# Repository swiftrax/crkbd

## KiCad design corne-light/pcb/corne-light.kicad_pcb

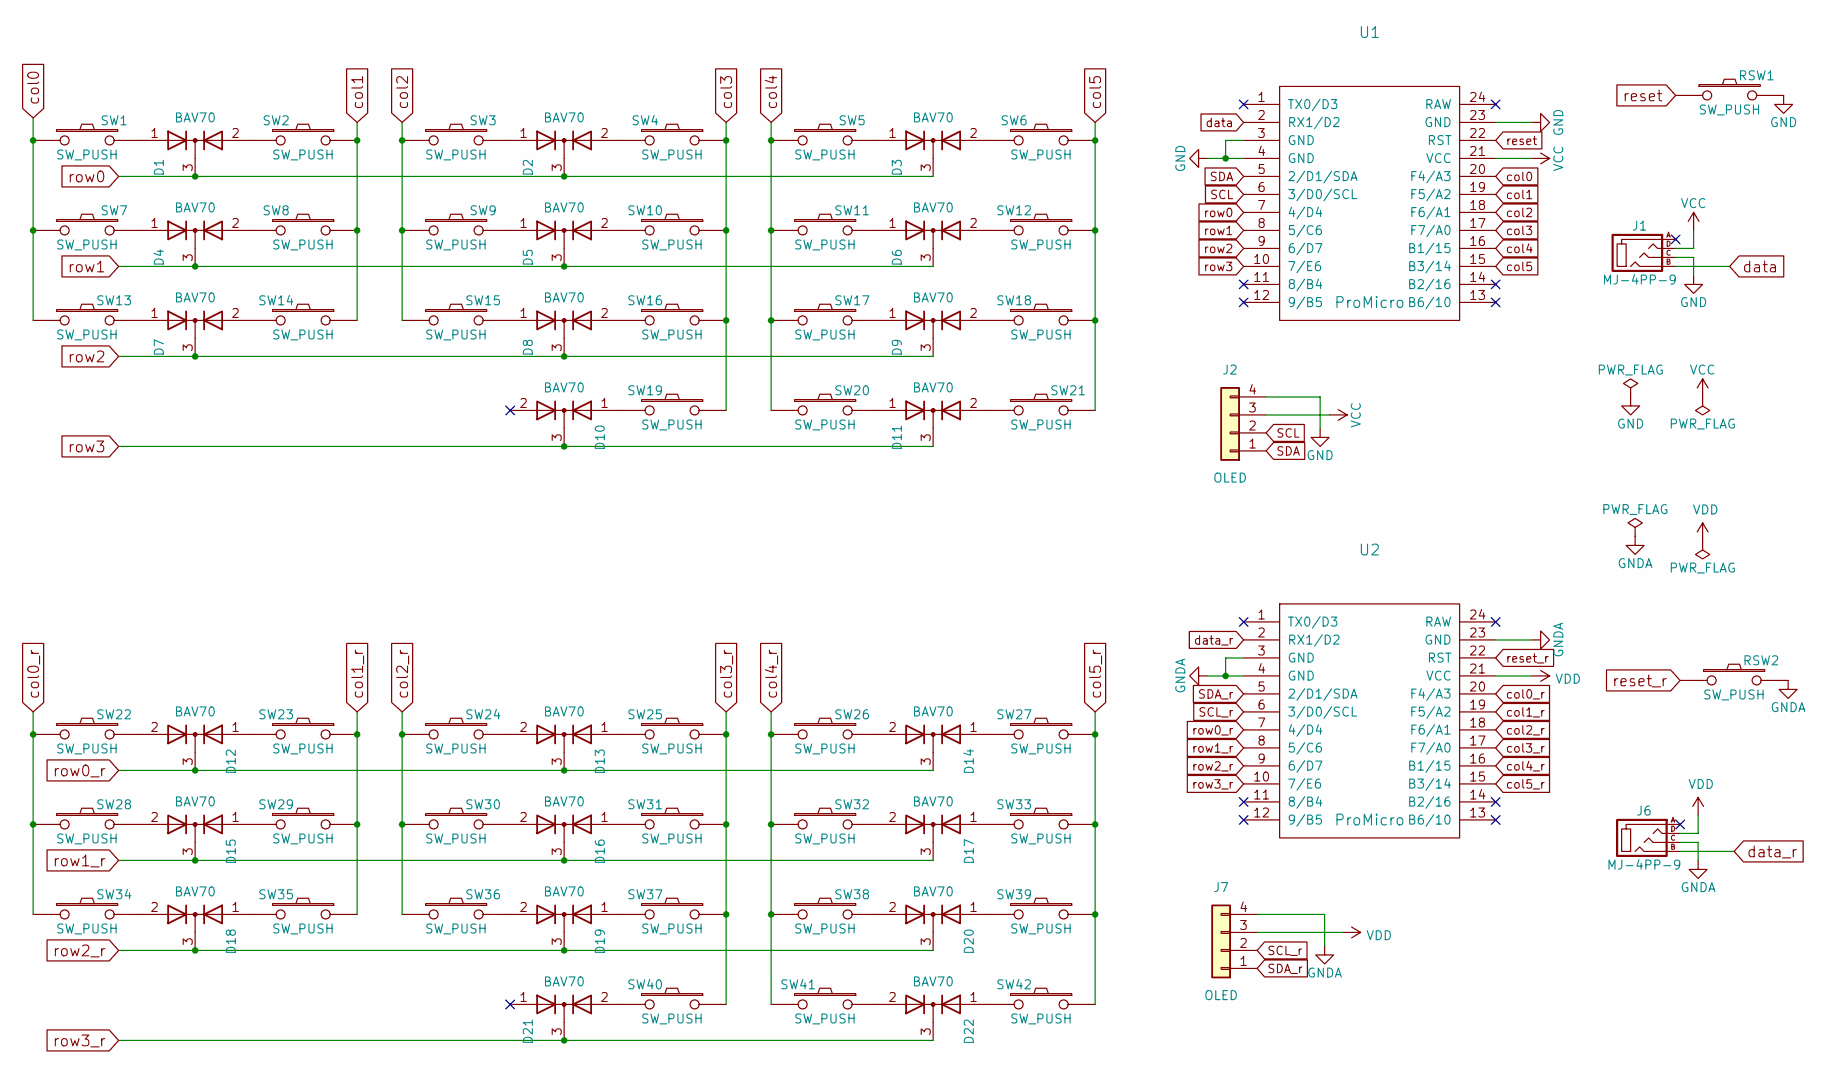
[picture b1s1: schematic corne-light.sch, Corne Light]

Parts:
D1, D2, D3, D4, D5, D6, D7, D8, D9, D10, D11, D12, D13, D14, D15, D16, D17, D18, D19, D20, D21, D22: BAV70; SOT-23_Annotated
J1, J6: MJ-4PP-9; MJ-4PP-9_1side
J2, J7: OLED; OLED_1side
RSW1, RSW2: SW_PUSH; ResetSW_1side
SW1, SW2, SW3, SW4, SW5, SW6, SW7, SW8, SW9, SW10, SW11, SW12, SW13, SW14, SW15, SW16, SW17, SW18, SW19, SW20, SW22, SW23, SW24, SW25, SW26, SW27, SW28, SW29, SW30, SW31, SW32, SW33, SW34, SW35, SW36, SW37, SW38, SW39, SW40, SW41: SW_PUSH; MXOnly-1U-NoLED
SW21, SW42: SW_PUSH; MXOnly-1.5U-NoLED
U1, U2: ProMicro; ProMicro_v3

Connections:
GND: J1.C, J2.4, RSW1.2, U1.3 (GND), U1.4 (GND), U1.23 (GND)
GNDA: J6.C, J7.4, RSW2.2, U2.3 (GND), U2.4 (GND), U2.23 (GND)
unnamed: D1.1 (A), SW1.2
unnamed: D1.2 (A), SW2.2
unnamed: D2.1 (A), SW3.2
unnamed: D2.2 (A), SW4.2
unnamed: D3.1 (A), SW5.2
unnamed: D3.2 (A), SW6.2
unnamed: D4.1 (A), SW7.2
unnamed: D4.2 (A), SW8.2
unnamed: D5.1 (A), SW9.2
unnamed: D5.2 (A), SW10.2
unnamed: D6.1 (A), SW11.2
unnamed: D6.2 (A), SW12.2
unnamed: D7.1 (A), SW13.2
unnamed: D7.2 (A), SW14.2
unnamed: D8.1 (A), SW15.2
unnamed: D8.2 (A), SW16.2
unnamed: D9.1 (A), SW17.2
unnamed: D9.2 (A), SW18.2
unnamed: D10.1 (A), SW19.2
unnamed: D11.1 (A), SW20.2
unnamed: D11.2 (A), SW21.1
unnamed: D12.1 (A), SW23.2
unnamed: D12.2 (A), SW22.2
unnamed: D13.1 (A), SW25.2
unnamed: D13.2 (A), SW24.2
unnamed: D14.1 (A), SW27.2
unnamed: D14.2 (A), SW26.2
unnamed: D15.1 (A), SW29.2
unnamed: D15.2 (A), SW28.2
unnamed: D16.1 (A), SW31.2
unnamed: D16.2 (A), SW30.2
unnamed: D17.1 (A), SW33.2
unnamed: D17.2 (A), SW32.2
unnamed: D18.1 (A), SW35.2
unnamed: D18.2 (A), SW34.2
unnamed: D19.1 (A), SW37.2
unnamed: D19.2 (A), SW36.2
unnamed: D20.1 (A), SW39.2
unnamed: D20.2 (A), SW38.2
unnamed: D21.2 (A), SW40.2
unnamed: D22.1 (A), SW42.2
unnamed: D22.2 (A), SW41.1
SCL: J2.2, U1.6 (3/D0/SCL)
SCL_r: J7.2, U2.6 (3/D0/SCL)
SDA: J2.1, U1.5 (2/D1/SDA)
SDA_r: J7.1, U2.5 (2/D1/SDA)
VCC: J1.D, J2.3, U1.21 (VCC)
VDD: J6.D, J7.3, U2.21 (VCC)
col0: SW1.1, SW7.1, SW13.1, U1.20 (F4/A3)
col0_r: SW22.1, SW28.1, SW34.1, U2.20 (F4/A3)
col1: SW2.1, SW8.1, SW14.1, U1.19 (F5/A2)
col1_r: SW23.1, SW29.1, SW35.1, U2.19 (F5/A2)
col2: SW3.1, SW9.1, SW15.1, U1.18 (F6/A1)
col2_r: SW24.1, SW30.1, SW36.1, U2.18 (F6/A1)
col3: SW4.1, SW10.1, SW16.1, SW19.1, U1.17 (F7/A0)
col3_r: SW25.1, SW31.1, SW37.1, SW40.1, U2.17 (F7/A0)
col4: SW5.1, SW11.1, SW17.1, SW20.1, U1.16 (B1/15)
col4_r: SW26.1, SW32.1, SW38.1, SW41.2, U2.16 (B1/15)
col5: SW6.1, SW12.1, SW18.1, SW21.2, U1.15 (B3/14)
col5_r: SW27.1, SW33.1, SW39.1, SW42.1, U2.15 (B3/14)
data: J1.B, U1.2 (RX1/D2)
data_r: J6.B, U2.2 (RX1/D2)
reset: RSW1.1, U1.22 (RST)
reset_r: RSW2.1, U2.22 (RST)
row0: D1.3 (K), D2.3 (K), D3.3 (K), U1.7 (4/D4)
row0_r: D12.3 (K), D13.3 (K), D14.3 (K), U2.7 (4/D4)
row1: D4.3 (K), D5.3 (K), D6.3 (K), U1.8 (5/C6)
row1_r: D15.3 (K), D16.3 (K), D17.3 (K), U2.8 (5/C6)
row2: D7.3 (K), D8.3 (K), D9.3 (K), U1.9 (6/D7)
row2_r: D18.3 (K), D19.3 (K), D20.3 (K), U2.9 (6/D7)
row3: D10.3 (K), D11.3 (K), U1.10 (7/E6)
row3_r: D21.3 (K), D22.3 (K), U2.10 (7/E6)

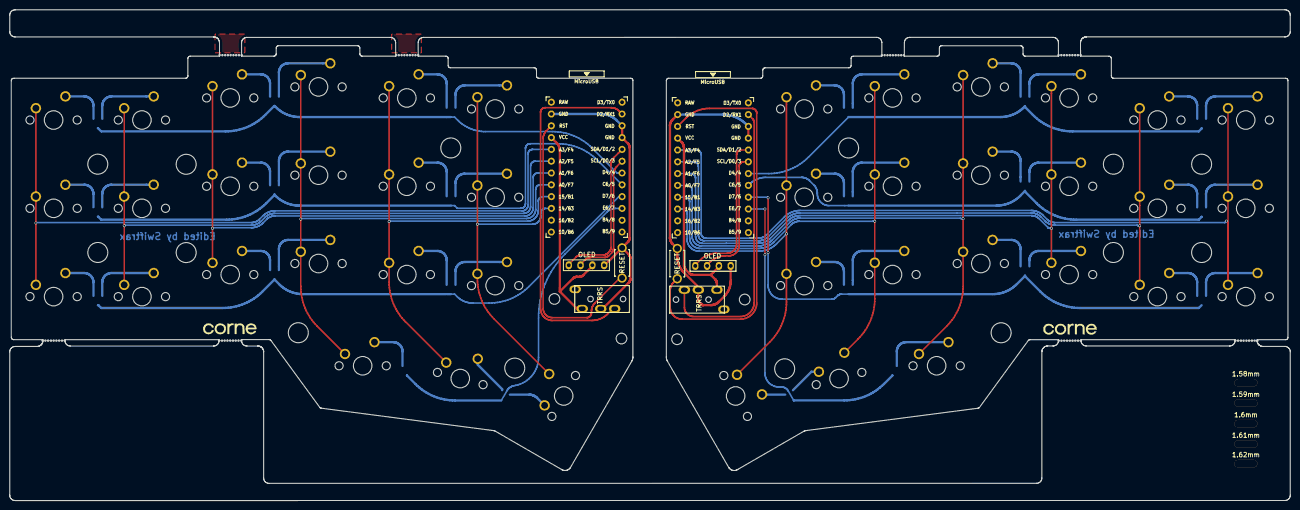
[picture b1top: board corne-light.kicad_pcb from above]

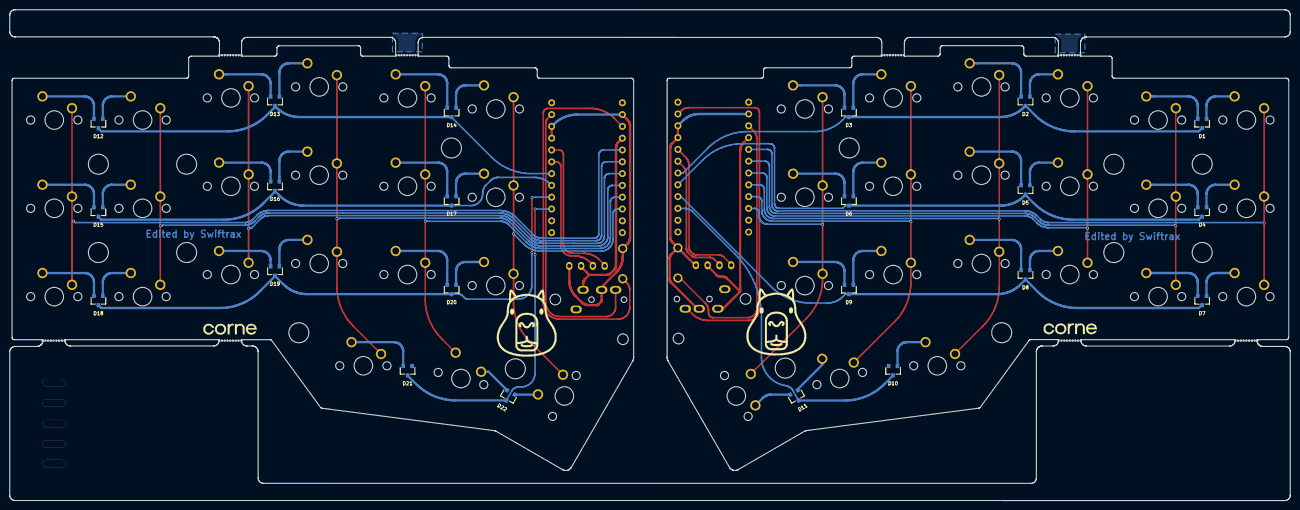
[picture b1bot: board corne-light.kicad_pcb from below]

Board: 2 copper layers, 275.5 x 105.6 mm, 98 parts (38 on the bottom side), 74 nets.

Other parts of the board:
J5, J5#2, J5#3, J5#4, J5#5, J5#6, J5#7, J5#8: Breakaway_Tabs
Ref**: Val**; spacer_m2
Ref**#2, Ref**#3, Ref**#4, Ref**#9, Ref**#10, Ref**#11, Ref**#12, Ref**#13, Ref**#14, Ref**#15, Ref**#16, Ref**#17, Ref**#18: Val**; spacer_m2
Ref**#5, Ref**#6, Ref**#7, Ref**#8: Val**; thread_m2

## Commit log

2020-11-28 Remove things im not using
2020-11-28 Change to CCDs
2020-11-28 Place CCDs
2020-11-28 Route mcu
2020-11-28 Curve cols
2020-11-30 Route matrix and others
2020-11-30 Add new text
2020-11-30 Make Gerbers
2021-01-06 Change Art
